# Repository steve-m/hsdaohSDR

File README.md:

# hsdaohSDR - SDR prototype with 90 MHz bandwidth

This repository contains the KiCad hardware design files for the SDR prototype that was shown during the [hsdaoh](https://github.com/steve-m/hsdaoh) [talk at OsmoDevcon 2024](https://media.ccc.de/v/osmodevcon2024-200-low-cost-high-speed-data-acquisition-over-hdmi).

It is to be used with the 'sdr' branches of both the hsdaoh and hsdaoh-fpga repository:

https://github.com/steve-m/hsdaoh/tree/sdr

https://github.com/steve-m/hsdaoh-fpga/tree/sdr

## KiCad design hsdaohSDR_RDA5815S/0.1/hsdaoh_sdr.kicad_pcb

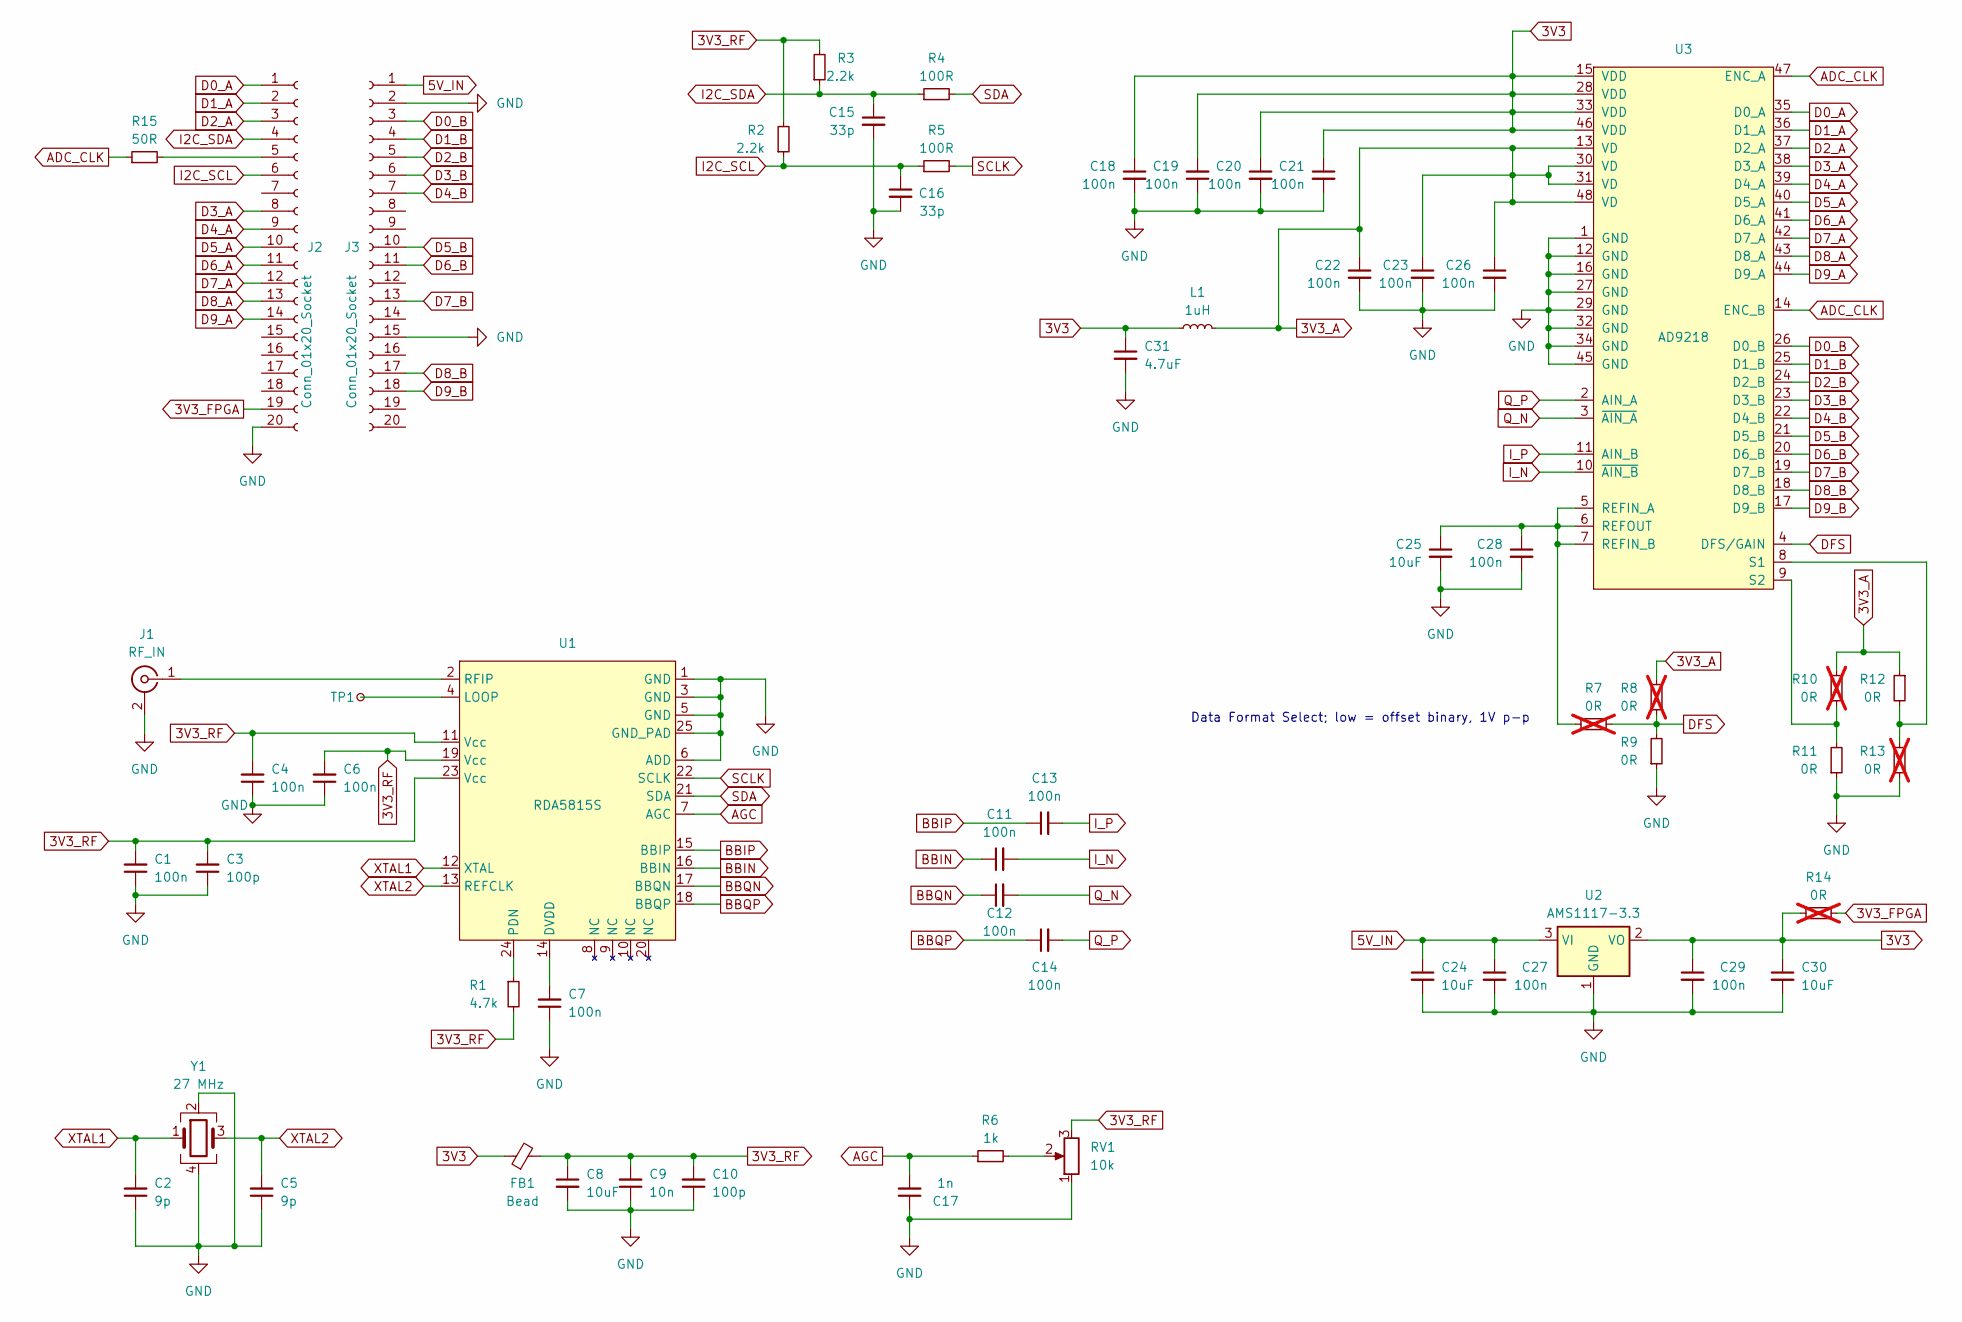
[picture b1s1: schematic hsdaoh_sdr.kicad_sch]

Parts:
C1, C4, C6, C7, C11, C12, C13, C14, C18, C19, C20, C21, C22, C23, C26, C27, C28, C29: 100n; C_0402_1005Metric
C2, C5: 9p; C_0402_1005Metric
C3, C10: 100p; C_0402_1005Metric
C8, C24, C30: 10uF; C_0805_2012Metric
C9: 10n; C_0402_1005Metric
C15, C16: 33p; C_0402_1005Metric
C17: 1n; C_0402_1005Metric
C25: 10uF; C_0603_1608Metric
C31: 4.7uF; C_0603_1608Metric
FB1: Bead; R_0603_1608Metric
J1: RF_IN; SMA_Molex_73251-1153_EdgeMount_Horizontal
J2, J3: Conn_01x20_Socket; PinSocket_1x20_P2.54mm_Vertical
L1: 1uH; L_0603_1608Metric
R1: 4.7k; R_0402_1005Metric
R2, R3: 2.2k; R_0402_1005Metric
R4, R5: 100R; R_0402_1005Metric
R6: 1k; R_0402_1005Metric
R7, R8, R10, R13: 0R; R_0402_1005Metric; not fitted
R9, R11, R12: 0R; R_0402_1005Metric
R14: 0R; R_0603_1608Metric; not fitted
R15: 50R; R_0402_1005Metric
RV1: 10k; Potentiometer_Bourns_TC33X_Vertical
TP1: TestPoint_Small; TestPoint_Pad_D1.0mm
U1: RDA5815S; QFN-24-1EP_4x4mm_P0.5mm_EP2.15x2.15mm_ThermalVias
U2: AMS1117-3.3; SOT-223-3_TabPin2
U3: AD9218; LQFP-48; Farnell 2376664
Y1: 27 MHz; Crystal_SMD_3225-4Pin_3.2x2.5mm

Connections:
3V3: C18.1, C19.2, C20.1, C21.1, C29.1, C30.1, C31.1, FB1.1, L1.1, R14.2, U2.2 (VO), U3.15 (VDD), U3.28 (VDD), U3.33 (VDD), U3.46 (VDD)
3V3_A: C22.1, C23.1, C26.1, L1.2, R8.2, R10.2, R12.1, U3.13 (VD), U3.30 (VD), U3.31 (VD), U3.48 (VD)
3V3_FPGA: J2.19, R14.1
3V3_RF: C1.2, C3.2, C4.2, C6.2, C8.1, C9.2, C10.2, FB1.2, R1.2, R2.2, R3.2, RV1.3, U1.11 (Vcc), U1.19 (Vcc), U1.23 (Vcc)
5V_IN: C24.1, C27.1, J3.1, U2.3 (VI)
ADC_CLK: R15.1, U3.14 (ENC_B), U3.47 (ENC_A)
AGC: C17.2, R6.1, U1.7 (AGC)
BBIN: C11.1, U1.16 (BBIN)
BBIP: C13.1, U1.15 (BBIP)
BBQN: C12.1, U1.17 (BBQN)
BBQP: C14.1, U1.18 (BBQP)
D0_A: J2.1, U3.35 (D0_A)
D0_B: J3.3, U3.26 (D0_B)
D1_A: J2.2, U3.36 (D1_A)
D1_B: J3.4, U3.25 (D1_B)
D2_A: J2.3, U3.37 (D2_A)
D2_B: J3.5, U3.24 (D2_B)
D3_A: J2.8, U3.38 (D3_A)
D3_B: J3.6, U3.23 (D3_B)
D4_A: J2.9, U3.39 (D4_A)
D4_B: J3.7, U3.22 (D4_B)
D5_A: J2.10, U3.40 (D5_A)
D5_B: J3.10, U3.21 (D5_B)
D6_A: J2.11, U3.41 (D6_A)
D6_B: J3.11, U3.20 (D6_B)
D7_A: J2.12, U3.42 (D7_A)
D7_B: J3.13, U3.19 (D7_B)
D8_A: J2.13, U3.43 (D8_A)
D8_B: J3.17, U3.18 (D8_B)
D9_A: J2.14, U3.44 (D9_A)
D9_B: J3.18, U3.17 (D9_B)
DFS: R7.1, R8.1, R9.2, U3.4 (DFS/GAIN)
GND: C1.1, C2.1, C3.1, C4.1, C5.1, C6.1, C7.1, C8.2, C9.1, C10.1, C15.2, C16.2, C17.1, C18.2, C19.1, C20.2, C21.2, C22.2, C23.2, C24.2, C25.2, C26.2, C27.2, C28.2, C29.2, C30.2, C31.2, J1.2 (Ext), J2.20, J3.2, J3.15, R9.1, R11.1, R13.2, RV1.1, U1.1 (GND), U1.3 (GND), U1.5 (GND), U1.6 (ADD), U1.25 (GND_PAD), U2.1 (GND), U3.1 (GND), U3.12 (GND), U3.16 (GND), U3.27 (GND), U3.29 (GND), U3.32 (GND), U3.34 (GND), U3.45 (GND), Y1.2, Y1.4
I2C_SCL: C16.1, J2.6, R2.1, R5.1
I2C_SDA: C15.1, J2.4, R3.1, R4.1
I_N: C11.2, U3.10 (~AIN_B)
I_P: C13.2, U3.11 (AIN_B)
unnamed: J1.1 (In), U1.2 (RFIP)
unnamed: J2.5, R15.2
unnamed: R6.2, RV1.2
unnamed: C7.2, U1.14 (DVDD)
unnamed: TP1.1, U1.4 (LOOP)
unnamed: R1.1, U1.24 (PDN)
unnamed: C25.1, C28.1, R7.2, U3.5 (REFIN_A), U3.6 (REFOUT), U3.7 (REFIN_B)
unnamed: R12.2, R13.1, U3.8 (S1)
unnamed: R10.1, R11.2, U3.9 (S2)
Q_N: C12.2, U3.3 (~AIN_A)
Q_P: C14.2, U3.2 (AIN_A)
SCLK: R5.2, U1.22 (SCLK)
SDA: R4.2, U1.21 (SDA)
XTAL1: C2.2, U1.12 (XTAL), Y1.1
XTAL2: C5.2, U1.13 (REFCLK), Y1.3

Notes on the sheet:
Data Format Select; low = offset binary, 1V p-p

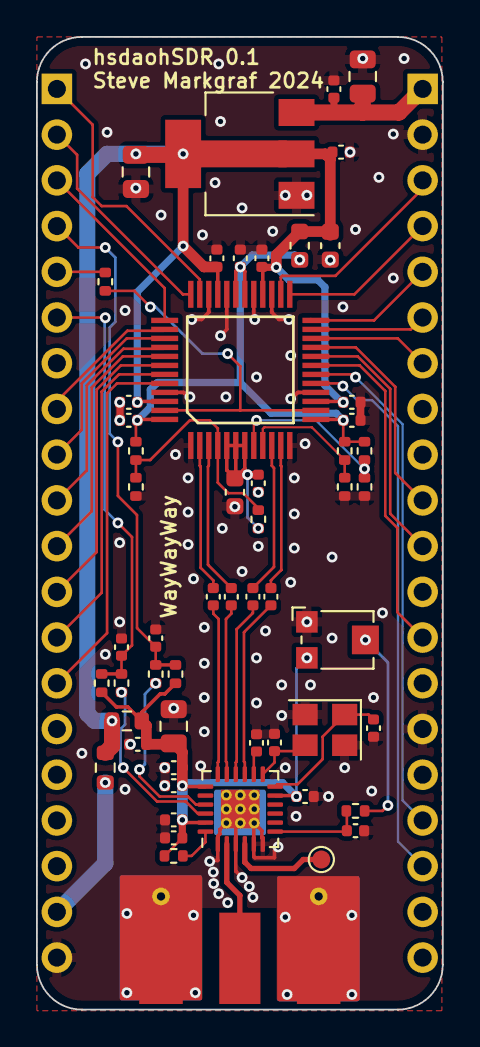
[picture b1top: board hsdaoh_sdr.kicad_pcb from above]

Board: 2 copper layers, 22.5 x 54.0 mm, 57 parts (0 on the bottom side), 52 nets.
